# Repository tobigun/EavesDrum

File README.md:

<p align="center">
  No matter if you are E(a)ve or Ste(a)ve - drumming for e(a)veryone
</p>

<p align="center">

</p>

<!-- vscode-markdown-toc -->
- [Welcome to EavesDrum!](#welcome-to-eavesdrum)
  - [Downloads](#downloads)
  - [EavesDrum Trigger Module](#eavesdrum-trigger-module)
- [Features](#features)
- [Before You Start: Is EavesDrum What You Need?](#before-you-start-is-eavesdrum-what-you-need)
- [Getting Started](#getting-started)
- [Build Your Own EavesDrum Trigger Module](#build-your-own-eavesdrum-trigger-module)
  - [Use the Reference Design](#use-the-reference-design)
    - [PCB Ordering and Assembly](#pcb-ordering-and-assembly)
    - [Connector Harness](#connector-harness)
      - [Connector Module](#connector-module)
      - [Build your own adapter](#build-your-own-adapter)
      - [Wiring the Single Pad Connectors](#wiring-the-single-pad-connectors)
  - [Make Your Own Design](#make-your-own-design)
    - [How the Circuit Works](#how-the-circuit-works)
      - [Over-Voltage Protection](#over-voltage-protection)
      - [Voltage Divider / DC Voltage Offset Generator](#voltage-divider--dc-voltage-offset-generator)
      - [Example](#example)
- [Configuration](#configuration)
  - [Calibration](#calibration)
  - [Settings](#settings)
    - [Generic Settings](#generic-settings)
    - [Pedal Settings](#pedal-settings)
    - [Apply Presets](#apply-presets)
  - [Mappings](#mappings)
  - [Apply a Whole Configuration](#apply-a-whole-configuration)
- [Understand and Reduce Latency](#understand-and-reduce-latency)
  - [Reduce Hit Detection Latency](#reduce-hit-detection-latency)
  - [Reduce Audio Interface Latency](#reduce-audio-interface-latency)
  - [TL;DR](#tldr)
- [Firmware Development](#firmware-development)
  - [How to Build the UI](#how-to-build-the-ui)
  - [How to Build the Backend and Firmware](#how-to-build-the-backend-and-firmware)
  - [How to Simulate a Drum-Kit on a PC](#how-to-simulate-a-drum-kit-on-a-pc)
- [FAQ](#faq)
    - [Windows 10 NCM device driver](#windows-10-ncm-device-driver)
- [About This Project](#about-this-project)
- [Other Related Projects](#other-related-projects)
- [Libraries](#libraries)
- [Author](#author)
- [License](#license)

<!-- vscode-markdown-toc-config
	numbering=false
	autoSave=true
	/vscode-markdown-toc-config -->
<!-- /vscode-markdown-toc -->

## Welcome to EavesDrum!

EavesDrum is an open-source e-drum trigger module project designed for drummers and makers.

It allows you to connect a multitude of drum pads or piezo triggers and convert their signals into MIDI events.

The configuration of the module is simple and user-friendly, thanks to a built-in WebUI. You can adjust sensitivity, threshold, and other parameters directly from your browser—no need for complicated software or direct hardware programming.

The trigger module acts as a USB MIDI device - simply connect it to your notebook and use drum software of your choice (EZdrummer, Addictive Drums, SSD5, ...) to convert your notebook into a complete drum module.

### Downloads
- Trigger Module:
  - [PCB files](https://github.com/tobigun/EavesDrum/releases/tag/PCB-module-v1.1.1)
  - [Firmware](https://github.com/tobigun/EavesDrum/releases/latest)
- [DIY Optical Hi-Hat Sensor](doc/hihat.md)

### EavesDrum Trigger Module

DIY ultra-low-volume metal mesh cymbal setup:

Conventional rubber cymbal setup:

Low-volume cymbal setup:

System overview:

## Features

- **Drum Trigger Inputs:**
  - With the EavesDrum PCB, you can connect your drum pads or piezo sensors to 32 analog inputs.
  - Each input can be mapped individually, for example to 16 TRS (3-pin Tip-Ring-Sleeve) connectors or 32 TS (2-pin Tip-Sleeve) connectors.
  - The [default configuration](#connector-harness) uses the following drum setup:
    - Snare (1x TRS for head/rim + 1x TS for side-rim)
    - 5x Toms (each with 1 TRS for head/rim)
    - Kick drum (1x TS)
    - Ride (1x TRS for bow/edge + 1x TS for cup)
    - 4x Cymbals (each with 1x TRS for bow/edge + 1x TS for cup)
    - Hi-Hat (1x TRS for bow/edge + 1x TS for cup)
    - Hi-Hat Pedal resistive or optical (connected to a dedicated connector with 3.3V or 5V supply voltage)
- **Compatibility:**
  -  EavesDrum is compatible with a wide range of [Roland (only non-USB), Yamaha, ATV and EFNOTE pads](#pad-connectors).
  -  The following pads were tested:
     - ATV XD-P10M/P13M 2-zone Drums
     - ATV aD-C14/C16/C18 3-zone Cymbals
     - EFNOTE EFD-S12P 3-zone Snare (head, rim, side-rim)
     - Roland PDX-8 2-zone Drum
     - Roland KD-10 Kick Pad
     - Zeitgeist ZG ECP 13" 3-zone Cymbal
     - Zeitgeist ZG CAD Cymbals (although the edge triggers unreliably due to the switch design)
     - Zeitgeist ZG ZKD7 Kick Pad
     - Drum-tec Hi-Hat controller (resistive)
     - DIY optical sensor (TCRT5000 based)
       - See sections below for schematics and Gerber files.
     - DIY drums and cymbals
       - See sections below for schematics and Gerber files.
- **MIDI Output:**
  - USB Device (Default)
    - Connect EavesDrum to a PC and use a Drum Software like EZdrummer or Superior Drummer to convert the trigger signals to high quality drum sounds. 
  - USB Host
    - Connect a USB device to EavesDrum, e.g. a Drum Module and trigger sounds on that device
      - Tested with a Yamaha EAD-10
      - Device must be compatible with USB Full-Speed device. This does not apply to EFNOTE's 3/5/7 devices as they require a USB High-Speed device.
  - DIN 5-Pin
    - Connect legacy drum modules or devices that still have a DIN 5-pin connector and trigger sounds on them.
  - Bluetooth LE Client (Pico2W only)
    - This can be used to connect to a device that can act as a Bluetooth LE MIDI Server, e.g. EFNOTE's 3/5/7 drum modules.
  - Bluetooth LE Server (Pico2W only)
    - Activate the BLE Server mode and connect a smartphone or tablet to EavesDrum and trigger sounds in an app. This can also be used to connect a computer wireless.
      - Android (smartphone): works, but most MIDI apps will require the "MIDI+BTLE" app to use BLE as they do not support it directly.
      - Windows (PC): does not support BLE MIDI out-of-the-box. You will need a BLE connector app like [BLE-MIDI Bridge](https://github.com/Maxime-J/BLE-MIDI-Bridge) or [MIDIberry](https://apps.microsoft.com/detail/9n39720h2m05) together with a virtual loopback MIDI cable software like [loopMIDI](https://www.tobias-erichsen.de/software/loopmidi.html).
      - iOS (iPad): works with Garage Band out of the box
  - Guitar Hero Drum-Kit (SPI)
    - If you have an old Guitar Hero Drum-Kit (e.g. for the Wii), attach EavesDrum to the controllers internal SPI connector and play Guitar Hero on your retro console with your modern drum kit.
- **MIDI Mappings:** 
  - Mappings are freely customizable via the UI.
  - It already contains Midi-Mappings for:
    - Addictive Drums 2
    - BFD Player 1.2
    - EZdrummer 3 (which can probably also be used as a base for your own Superior Drummer 3 mapping)
    - Superior Drummer 3
    - MT Power 2
    - Steven Slate Drums 5 (SSD5)
- **Low Latency:**
  - Latency is mainly determined by your audio interface and the selected scan time. With a decent audio interface, you can [reach a total latency of about 8ms](#latency).
  - You can measure the latency of your setup with the latency measurement feature built into the UI.
- **Affordable:** you might be able to make an assembled trigger module for approx. 20€.
  - See the section [Build your own EavesDrum trigger module](#use-the-reference-design).
- **Supported Microcontrollers:**
  - Raspberry Pi Pico2
  - Raspberry Pi Pico2W (comes with a WIFI and Bluetooth module)
    - Required for MIDI over Bluetooth LE.
    - Also provides a WIFI Access Point to reach the EavesDrum WebUI wirelessly. 

- **Open Source:** Source code and PCB Gerber files are available for customization and extension.
- **WebUI Configuration:** Browser-based interface for setting up and tweaking trigger parameters such as sensitivity, threshold, retrigger prevention, and more. No app required as the UI runs directly on the trigger module.
  - Monitor the signal of your drum pads in real time so that you can see the effect of your settings.

  - Provides extensive settings options within a (hopefully) user-friendly layout.

  - Mappings can be adjusted individually or for the whole kit.

## Before You Start: Is EavesDrum What You Need?
**EavesDrum is for you if you:**
  - need more / additional trigger inputs to those that standard drum kits support.
  - want to mix drums from different vendors as most drum kits only work well with their own pads.
  - want to start drumming and do not want to pay a fortune for a drum kit.
  - want to diagnose or improve the trigger behavior of your drum pad.
  - have fun making stuff and just want to build your own drum kit or implement your own drum module features.

**EavesDrum might not be for you if you:**
  - want to use the module for live performances as it does not give any guarantee error-free operation at all times or conditions.
  - want a drum module that works standalone without a Notebook.
  - want a drum module that works out-of-the-box, as you will have to tweak the settings according to your pads via the UI.
  - need cross-talk cancelation, positional sensing or decay curves, as these features are not implemented (yet).

> [!IMPORTANT]
> **Disclaimer:** Although EavesDrum has been tested with various drum pads and setups, it remains a DIY hardware project and may behave differently depending on your specific configuration. Connecting this module to your equipment is done at your own risk. I cannot be held liable for any damage, malfunction, or injury resulting from its use. Please ensure compatibility and take appropriate precautions before integrating it into your setup.

## Getting Started

0. **Prerequisites:**
All you need is:
    - A computer with a drum software (see [MIDI Mappings](#midi-mappings) to give you a short overview).
      - A PC or Mac is recommended.
        - Although there is no minimum requirement, a slow CPU might increase the [Latency](#latency).
        - USB and Bluetooth LE is supported
      - An Apple iPad with Garage Band also works - either with USB-C (or an Apple Camera Connection Kit for Lightning connectors) or with Bluetooth LE.
      -  Android smartphones / tablets also work (via USB or Bluetooth LE) but lack good drumming apps.
    - A decent audio interface with low latency, preferably one with dedicated ASIO drivers. See [the section about latency](#latency) for more information.
    - Something to drum on, i.e. drum pads, cymbals and a Hi-Hat pedal. Or just a cheap piezo if you want to DIY your own drum.

1. **Build the EavesDrum trigger module:**<br/>
   - Either built it yourself or order it via a PCB manufacturer of your choice.
   - See section [Build your own EavesDrum trigger module](#use-the-reference-design) for schematics and Gerber files.

2. **Download & Flash the firmware:**<br/>
   - [Download the firmware for your Pico board from the Release download section](https://github.com/tobigun/EavesDrum/releases/latest).
   - Press the BOOTSEL while connecting your Pico Board via USB to enter the bootloader mode.
   - The board will now be detected as an USB flash drive.
   - Drag & Drop the firmware .uf2 file onto the drive.
3. **Start the WebUI:**<br/>
   - Connect EavesDrum to a computer, tablet or smartphone
     - via USB: EavesDrum will be detected as a network device
     - via WIFI AccessPoint (only with Pico2W)
       - The AccessPoint (AP) can be activated by pressing and holding the WIFI button at power-up until the network LED lights up. For security and performance reasons, the AP is only active for one session until the module is powered down.
       - Connect to the AP named "EavesDrum". No credentials are required.
   - Open your browser and navigate to the WebUI by entering either
     - the static IP: http://192.168.7.1 (USB) or http://192.168.4.1 (WIFI AP)
     - the DNS name http://eaves.drum</a>.
     - **IMPORTANT**: if you are using Windows 10 you have to install the USB network drivers manually to reach the WebUI. See the [FAQ](#faq) section below for more info. 
4. **Calibrate:**<br/>
   - [Calibrate the voltage offset with the UI Wizard](#calibration)
5. **Connect Drums:**<br/>
   - Connect your drum pads or triggers to the EavesDrum hardware.
6. **Configuration:**<br/>
   - Adjust [settings](#settings) and [MIDI mappings](#mappings).
7. **Play:**<br/>
   - Once configured, start playing and enjoy!

## Build Your Own EavesDrum Trigger Module
### Use the Reference Design
**Schematics of the trigger module with 32 inputs:**

You can find the schematics and pcb files in the `schematics/module` directory. They can be viewed and edited with [KiCad](https://www.kicad.org/).

**Bill of material (BOM):**

| Component | Designator | Quantity | Price / Unit | Price Total | Comment |
| --------- | ---------- | -------- | ------------ | ----------- | ------- | 
| Raspberry Pi Pico 2(W)(H) | A1 | 1 | 5€ / W: 7.50€ | 5€ / W: 7.50€ | Use a Pico2W if you want WiFi and Bluetooth LE, otherwise a Pico2 is enough.<br>- There is also a "H" variant for ~1€ more with an already soldered header<br>- Pico1 is not recommended due its outdated performance. |
| 20-pin Header (male)<br>20-pin Header (female) | J4, J5 | 2 | 0.20€<br>0.30€ | 1.00€ | Optional but recommended. <br>- Socket your Pico so that it can be replaced if it is damaged or if you want to exchange it by another variant.<br>- The male header is not needed if one of the Pico "H" variants is used. |
| HC4067 | U1, U2 | 2 | 1.00€ | 2.00€ | Multiplexer. Each provides 16 inputs.<br>Available from many vendors with HC4067 in the name (e.g. CD74HC4067M). Make sure it is the SO-24 package. |
| BAT54S | D1.0 - D1.15<br>D2.0 - D2.15 | 32 | 0.05€ | 1.60€ |Prefer the ones with a forward voltage (VF) of 800mV@100mA over those with 1V@100mA but probably any vendor and type will work.|
| LED (red) | D3 | 1 | 0.08€ | 0.08€ | Use any color of your choice. THT or SMD 0805 / 0603 packages are supported. |
| LED (white/blue) | D4 | 1 | 0.10€ | 0.10€ | Use any color of your choice. THT or SMD 0805 / 0603 packages are supported. |
| LED (yellow) | D5 | 1 | 0.10€ | 0.10€ | Use any color of your choice. THT or SMD 0805 / 0603 packages are supported. |
| Push Switch | SW1, SW2, SW3 | 3 | 0.15€ | 0.45€ |6x6mm. Only the `RESET` button is used at the moment. |
| Potentiometer 5k | R3, R6 | 2 | 0.35€ | 0.70€ | Supports Piher PT10 (10mm) / PT6 (6mm) or Bourns TC33 (SMD) |
| Potentiometer 100k | R11 | 1 | 0.35€ | 0.35€ | Supports **only** Piher PT6 (6mm) or Bourns TC33 (SMD) |
| Resistor 10 Ohms | R17 | 1 | 0.03€ | 0.03€ | SMD 0805 package, 125mW, 1%.<br>For MIDI 5-pin DIN connector |
| Resistor 33 Ohms | R18 | 1 | 0.03€ | 0.03€ | SMD 0805 package, 125mW, 1%.<br>For MIDI 5-pin DIN connector |
| Resistor 330 Ohms | R5, R8, R13 | 3 | 0.03€ | 0.09€ | SMD 0805 package, 125mW, 1% |
| Resistor 1 kOhms | R1.0 - R1.15<br>R2.0 - R2.15 | 32 | 0.015€ | 0.48€ | SMD 0805 package, 125mW, 1% |
| Resistor 2.7 kOhms | R4 | 1 | 0.03€ | 0.03€ | SMD 0805 package, 125mW, 1% |
| Resistor 4.7 kOhms | R9, R14 | 2 | 0.03€ | 0.06€ | SMD 0805 package, 125mW, 1%.<br>Use different values to adjust brightness of LEDs D3 (R9) and D5 (R14) to your liking. |
| Resistor 10 kOhms | R10 | 1 | 0.03€ | 0.03€ | SMD 0805 package, 125mW, 1%<br>Use different value to adjust brightness of LED D4 to your liking. |
| Resistor 15 kOhms | R15, R16 | 1 | 0.03€ | 0.06€ | SMD 0805 package, 125mW, 1%.<br>For USB-Host connector |
| Capacitor 10 µF | C1, C2 | 2 | 0.04€ | 0.08€ | SMD 0805 package, >=25V, X5R (or X7R)
| D-Sub HD 44-pin Connector, right-angled, female | J0 | 1 | 2.50€ | 2.50€ | Alternatively, you can use any connector of your choice via the 2x25 pin IDC header (J2). |
| USB-A socket, right-angled | J1 | 1 | 0.15€ | 0.15€ | Socket for USB-Host. |
| Header 2x25 pins (male) | J2 | 1 | 0.33€ | 0.33€ | Expansion port (Optional).
| 3-Pin Header (female) | J3 | 1 | 0.15€ | 0.15€ | UART serial debug output.
| DIN 5-pin female 180° | J7 | 1 | 0.85€ | 0.85€ | Connector for MIDI Serial DIN Output. |
| PCB | - | 1 | ~5€ (Germany) | ~5€ | See the section [PCB Ordering and Assembly](#pcb-ordering-and-assembly) for more info|
| **Total** |||| ~22€ || 

If you are located in Germany, check prices at Reichelt (that's where the prices from above are from), Pollin, Conrad. Globally Mouser and Farnell might be your friend.

#### PCB Ordering and Assembly
All you need to order your Trigger Module PCB for assembly are the following files:
- GERBER File
- BOM File (Bill of Material)
- CPL File (Component Placement List)

These files are available on the [PCB Module 1.2 Release Page](https://github.com/tobigun/EavesDrum/releases/tag/PCB-module-v1.2).

**To order the PCB:**
- Open the website of a PCB manufacturer.
  - The most famous ones are probably JLCPCB and PCBWay from China.
  - There is also Aisler (Germany), EuroCircuits (Europe) and probably more if you want to produce your PCB in Europe instead of China.
  - Choose whatever suits you best.
- Upload the GERBER zip-file. The site should show you a preview of the PCB now.
- You can leave the default settings.
  - (Recommended) Change `Surface Finish` from `HASL (with lead)` to `LeadFree HASL` to protect our environment from toxic lead
- For delivery "EuroPacket" or "Global (Standard) Direct" might be your choice.
  - Both variants will ship your PCBs together with other PCBs in a big package to an importer in your home country (or a neighbored country). The package will then be split into smaller packages and sent to you. This is cheaper and will probably also save you the hassle of customs as this will be done by the importer.
  - The shipment time is a bit longer than with other more expensive delivery options. But with all options the parcel will probably spent several days in the customs office, so time savings is not that much noticable.

*Examples:*
- JLCPCB: 4€ - Coupons + Shipping/Taxes
  - Shipping to Germany: Global Standard Direct: 1.50€ / EuroPacket: 5.50€ + Tax: ~1€
- PCBWay: 5€ - Coupons + Shipping/Taxes
  - Shipping to Germany: ~5€ with Global Direct + Tax: ?

Due to the varying discount by coupons, prices of JLCPCB and PCBWay my vary. So check both.

**Assembly**
It is possible to assemble the PCB on your own by hand-soldering without special equipment. The only tricky part is the HC4067 SMD packages and the SMD resistors and capacitors. While the latter is quite easy, the HC4067 requires some experience.

You can also let JLCPCB or PCBWay assemble the PCB as you already order the PCB there.

*Example:*
- JLCPCB: 5 assembled PCBs including parts cost about 106€ (excl. shipping/tax), so approx. 21€ per PCB.
  - Note that the minimum amount of assembled PCBs per order is 2

If you want an assembled board it is best to organize a collective purchase order to split the cost. I created a [forum discussion where you can organize an order](https://github.com/tobigun/EavesDrum/discussions/1).

**To order an assembled PCB:**
- Perform the same steps as for the normal PCB but select "PCB Assembly".
- If you use JLCPCB in the next step you are asked for the BOM and CPL files that you have to upload.
- Some parts might currently not be available. There is most likely an identical component / chip from a different vendor that you can select in this case.
- In the next step check the component placements and submit your order.
- After a review an engineer might contact you if there are questions about the design (that was the case in my order).

> [!NOTE]
> Also take a look at the [DIY Optical Hi-Hat Sensor PCB](doc/hihat.md). You might want to get both PCBs with one order.

#### Connector Harness

In addition to the trigger module you will have to build an adapter to connect the drum pads.

##### Connector Module

The easiest way to achieve this is to build the connector module:

You can find more information about the connector and the files to order the (assembled) PCB on the  
[connector release page](https://github.com/tobigun/EavesDrum/releases/tag/PCB-connector-v1.0).

##### Build your own adapter

But you can also build your own adapter. Here is the pin out of the D-Sub HD 44 pin connector:

The pin names consist of the multiplexer input IDs (in1_x: input x of Multiplexer MP1, in2_x: input x of Multiplexer MP2).

You can either solder jacks directly to a D-Sub connector or you can build an adapter to one of the cable harnesses that come with drum modules.

This is the default configuration for the outputs:

| Jack | Pins | Assignment |
|-----------|------|------------|
|1| in1_0, in1_1, in1_2 | Snare (Main, Rim, Side-Rim) |
|2| in1_3, in1_4 | Tom 1 (Main, Rim) |
|3| in1_5, in1_6 | Tom 2 (Main, Rim) |
|4| in1_7, in1_8 | Tom 3 (Main, Rim) |
|5| in1_9 | Kick Drum |
|6| in1_10, in1_11, in1_12 | Ride (Bow, Edge, Cup) |
|7| in1_13, in1_14, in1_15 | Cymbal 1 (Bow, Edge, Cup) |
|8| in2_0, in2_1, in2_2 | Cymbal 2 (Bow, Edge, Cup) |
|9| in2_3, in2_4, in2_5 | Cymbal 3 (Bow, Edge, Cup) |
|10| in2_6, in2_7, in2_8 | Hi-Hat (Bow, Edge, Cup) |
|11| in2_9, in2_10 | Tom 4 (Main, Rim) |
|12| in2_11, in2_12 | Tom 5 (Main, Rim) |
|13| in2_13, in2_14, in2_15 | Cymbal 4 (Bow, Edge, Cup) |
|Pedal| adc2, +3.3V/5V (optical only) | Hi-Hat Pedal (resistive or optical)<br>- For resistive controllers: adjust the `ADC2 DC offset` potentiometer to the (+) direction (~4kOhm)<br>- For optical (TCRT5000) controllers: adjust the `ADC2 DC offset` potentiometer to the middle (~69kOhm)<br>This will adjust the sensitivity of the ADC2 channel. You can fine-tune this setting in the UI later. |

> [!INFO]
> The layout for the older D-Sub 37 pin connector of board revisions v1.1.x can be found [here](https://github.com/tobigun/EavesDrum/tree/PCB-module-v1.1.1#connector-harness)

##### Wiring the Single Pad Connectors

The wiring of **Snares and Toms** is straightforward in most cases
- Almost all companies use the Roland style 2-Piezo 1xTRS layout
- Yamaha uses switches for Edge and Side Rim
- EFNote adds a dedicated Side-Rim zone with another Piezo

<table>
<thead>
  <tr>
    <th>Tom/Snare</th>
    <th>Main/Head (Piezo)</th>
    <th>Edge</th>
    <th>Side-Rim</th>
    <th>EavesDrum Setting</th>
  </tr>
</thead>
<tbody>
  <tr><td>Generic 1-Zone</td><td>Tip</td><td>-</td><td>-</td><td>Drum / 1-Zone / Piezo</td></tr>
  <tr><td>Roland 2-Zone</td><td>Tip</td><td>Ring</td><td>- (Cross-Stick sound is generated by module)</td><td>Drum / 2-Zones / 2 Piezos</td></tr>
  <tr><td>Yamaha 3-Zone</td><td>Tip</td><td colspan='2'>Ring (Switches for zones are multiplexed by a 10k resistor)</td><td>Drum / 3-Zones / Piezo + 2 Switches (1x TRS)</td></tr>
  <tr><td>EFNOTE 3-Zone</td><td>Tip (Main Jack)</td><td>Ring (Main Jack)</td><td>Tip (Side-Rim Jack)</td><td>Drum / 3-Zones / 3 Piezos</td></tr>
</tbody>
</table>

**Cymbals** (with 3-Zones) follow two main connection styles:
- Roland style with 2x TRS Jacks (labeled "Bow/Edge" and "Bow/Bell")
- Yamaha style with 1x TRS Jack. Bell and Cup switch connected to the "Ring" pin (multiplexed by a 10k resistor)

If you have only a one or two zone cymbal the pin layout is the same for both vendors.

<table>
<thead>
  <tr>
    <th>Cymbal</th>
    <th>Bow (Piezo)</th>
    <th>Edge Switch</th>
    <th>Bell/Cup Switch</th>
    <th>EavesDrum Setting</th>
  </tr>
</thead>
<tbody>
  <tr><td>Generic 1-Zone</td><td>Tip</td><td>-</td><td>-</td><td>Cymbal / 1-Zone / Piezo / No Choke</td></tr>
  <tr><td>Generic 2-Zone</td><td>Tip</td><td>Ring</td><td>-</td><td>Cymbal / 2-Zones / Piezo + Switch / Choke: Edge</td></tr>
  <tr><td>Roland 3-Zone</td><td>Tip (Jack "Bow/Edge")</td><td>Ring (Jack "Bow/Edge")</td><td>Ring (Jack "Bow/Bell")</td><td>Cymbal / 3-Zones / Piezo + 2 Switches (<b>2x</b> TRS) / Choke: Edge</td></tr>
  <tr><td>Yamaha 3-Zone</td><td>Tip</td><td colspan='2'>Ring (multiplexed by a 10k resistor)</td><td>Cymbal / 3-Zones / Piezo + 2 Switches (<b>1x</b> TRS) / Choke: Edge</td></tr>
</tbody>
</table>

See also:
- [Cymbal wiring diagram at edrums.github.io](https://edrums.github.io/en/diy/cymbal_switch/) for the wiring difference between Roland and Yamaha cymbals.
- [Yamaha compatibility matrix](https://de.yamaha.com/de/download/files/2094396/) for an overview of the Tom and Cymbal models

### Make Your Own Design

In case you do not want to use the reference design or you just need a few inputs, you can also design your own trigger module and just use the firmware.
The base circuit for each input consists of the following parts:

Please note that "~2,7k" for R1 in the schematics means that the variable resistor should be adjusted to this value. The nominal value of the resistor should be about 5k to have some range for the adjustment.

You might also be able to build this on a breadboard for first experimentation.

#### How the Circuit Works
Skip this section if you are not interested in the electronic background of the circuit.

##### Over-Voltage Protection
- Two clamping diodes restrict the signal to the range between 0V - 3.3V
  - Protects the ADC input pins of the microcontroller
  - Prevents cross-talk between inputs if a Multiplexer (e.g. 74HC4067) is used
- Note that Schottky diodes with a low forward voltage have to be used here
  - They react faster than a conventional (Silicon P-N-junction) diode to over voltage spikes
  - The BAT85, BAS85 (SMD variant of the BAT85) and BAT54S (two diodes in one SMD package) diodes work fine

##### Voltage Divider / DC Voltage Offset Generator
- The resistors R1 and R2 form a voltage divider that halfs the operation voltage (Vcc=3.3V) to generate a ~1.65V DC offset voltage
  - This is necessary to sample the full signal with its positive and negative half-wave
  - Note that R1 is a variable resistor (potentiometer) as the circuit is usually not that perfect that R1=R2 gives you half the operation voltage as it should in theory
- Together with R3, R1 and R2 scale the voltage of the piezo to the range of 0V - 3.3V that can be sampled by the ADC
  - This is necessary as the voltages of a piezo can be rather high.
  - If you want to play with the values there is an [LTSpice simulation here](doc/simulation/drum-trigger.asc) but keep in mind that the piezo model does not act like a real one.
- Simpler approaches without an offset voltage are also possible, e.g. by just clamping the signal with a zener diode to just keep the positive half-wave of the signal
    - Although this works, you will have to pay attention to the polarity of the piezos
    - If the piezo starts with a negative half-wave, you will miss it and thus will add latency of approx. 1ms
    - This is even worse, if you use two piezos for head and rim, as the wrong zone might be triggered if the first half-wave of one piezo is missing but missing for the other.

##### Example
Here is a simple example with a high intensity hit on a snare drum: The left shows the input signal that is offset by 1.65V and it fits nicely into the 0V - 3.3V range. On the right you see the display in the UI. All the details of the signal are maintained. Note that the firmware maps the negative part of the signal to the positive y-axis so that the thresholds can be edited more easily.

## Configuration

### Calibration
Before you can start you have to first adjust the DC voltage offset so that the signal level is at 0% when no pad is hit. But no panic - the process is easy and only has to be done once.

For this open the WebUI, open the settings page (should be open by default) and click on `Calibrate` in the `Monitor` panel and follow the instructions.

At the beginning the signal graph will probably look like this, with a signal level above 0% (here 10%):

Now turn the potentiometer labeled `ADC0 DC offset` (R3) with a screwdriver. Only if turned in the correct direction, the signal level will decrease, otherwise it will increase. So turn the potentiometer until the signal level reaches 0%. If you turned too much, the signal level will increase again - in this case turn in the opposite direction.

The signal graph should now look like this - with a signal level of 0%:

Now the calibration is completed.

> [!NOTE]
> Do not worry if the signal is not totally clean and has a bit of a ripple in the 1% or 2% range. This can be compensated with the thresholds later.
> If you do not reach the 0% level at all, your trigger module might be faulty.

### Settings

To optimize the trigger behavior for your pad, go to the settings page and open the panel of the pad you want to adjust.

First assure that the Drum type (here: Drum / 3-Zones / 3 Piezos) is correct. If you are not sure, check [the section about the different pad connectors](#pad-connectors) to see what the type should be.

Mark the pad as monitored (the record button on the right top of the pad's panel). This way you can see the signal graph (left) and hit graph (right) in the `Monitor` panel whenever you hit the monitored pad. Right next to the hit graph is the hit history which shows you the last hits. You can also click on one of the last hits to see the graphs again.

If you click on `Show All Pads` on the top, you can see hits on every pad, no matter if it is monitored or not.

#### Generic Settings

- **Main/Head/Rim/Edge/Cup/... Range**: trigger range for each zone
  - The **min. value of the range** specifies the sensitivity.
    - You should set it as low as possible without having the pad trigger when you do not hit it.
  - The **max. value of the range** specifies the signal level that marks 100%.
    - Set it in a way that you can reach a signal level of 100% when you hit the pad the hardest way you would in your playing style.
    - If you set the max. too low, the detected signal level will be 100% even if you did not hit the pad with the highest intensity.
  - If you enable monitoring for the pad it should be easy to find the correct values.
  - For cymbals with switches for edge and cup you will only have a **minimum threshold** for each switch instead of a range.
    - This determines at which level the switch is considered to be closed or opened.

- **Scan Time**: Determines the time to search for a peak (Scan phase).
- **Mask Time**: Blocks hit detection for the given time (Mask phase).
  - Can be used to reduce false retriggers.
  - The Mask phase starts after the Scan phase.
  - The Mask is applied to all zones of the pad.
- **Decay Time**: Blocks hits with a hit velocity below the given decay curve (Decay phase).
  - In contrast to the Mask phase that blocks all hits, this only blocks hits selectively.
  - It can be used to define a longer decay phase where reverberations of the last hit can be blocked but new hits are still possible if they are strong enough.
  - The Decay phase starts after the Mask phase.
  - The Decay curve is applied to all zones of the pad.
- **Decay Curve**: The curve that defines how the detection threshold decreases during the decay phase.
  - **Linear**: The further the decay phase progresses, the lower the required hit strength becomes for a hit to be detected. 
    - The phase begins with a detection threshold equal to the highest signal value detected during the scan phase (the peak).
    - It ends with a detection threshold equal to the minimum detection threshold.
    - Throughout the decay phase, the threshold is linearly reduced from the peak value down to the minimum threshold.
- **Curve Type**: Lets you change the trigger behavior for low or high intensity hits, i.e. you can shift the sensitivity more to the lower or higher intensities.
- **Head/Rim Bias**: Sets whether to prefer head or rim sound when the signals of both to not indicate a clear winner.
  - This is useful to assure that rimshots trigger the rim sound.
  - Move the bias more to the rim (i.e. to the right), the rim zone will more likely be triggered if both zones were hit at once.
  - Only available for drums (i.e. snares and toms) with at least two zones.

> [!IMPORTANT]
> When you change settings they will be applied immediately but they will be reset to the old values when EavesDrum reboots or loses power. To keep the settings you have to save them with the "Save" Button (SD-Card icon) in the top Icon Bar.

#### Pedal Settings
The settings for the Hi-Hat pedal are different from the settings of the pads.

- **Pedal Range**: determines the offset and threshold for the lowest and highest signal level
  - Do not touch the Hi-Hat pedal for the open position.
  - Adjust the **min value** of the `Pedal Range` so that the corresponding marker in the monitor's signal graph is slightly above the current pedal signal and the Pedal value in the hit graph is at 0%.
  - Next, close the Hi-Hat pedal.
  - Now adjust the **max value** of the `Pedal Range` so that the corresponding marker in the monitor's signal graph is slightly below the current signal and the hit graph shows 100%.
  - When you move the pedal now, you should get the full range between 0% and 100% in the hit graph, and it should stay at 0% when open and at 100% when closed.
- **Move Detection Tolerance** this determines how much the pedal has to be moved to change its value. A smaller tolerance gives you a higher resolution but is more prone to noise in the signal.
  - Press the Hi-Hat pedal to a position between open and closed. Try to keep this position - the value in the hit graph should not change. If it does, you might decrease the tolerance until the hit graph value is stable.
- **Pedal State Thresholds** and **Chick Detect Timeout**:
  - When the pedal travels from the `Almost Closed` position to the `Closed Position` a "Chick" sound detection takes place.
  - The faster the pedal moves from `Almost Closed` to `Closed` the higher the intensity of the "Chick" sound will be.
  - If the time between both states is higher than **Chick Detect Timeout**, then no sound will be played.
  - If you do not want a "Chick" sound, you can disable it on the Mappings Page by setting the sound for the "Chick" to `None`.

To see the effect of the settings, monitor the pedal with the record button:

#### Apply Presets
In the folder `config/presets` you can find some presets for some pads. You can apply them by dragging them from Windows Explorer to the settings panel of a pad.

### Mappings

With the Mappings page you can change the MIDI mappings of each pad.

Select the MIDI note of the zone to the desired value. You can trigger the note via the UI by pressing the "Play" button to preview the sound.

> [!IMPORTANT]
> When you change mappings they will be applied immediately but they will be reset to the old values when EavesDrum reboots or loses power. To keep the settings you have to save them with the "Save" Button (SD-Card icon) in the top Icon Bar.

**Apply Drum-Kit Mappings**
You can change the mappings of all pads in the drum-kit at ones if you drag & drop a mapping file (see folder `/config/mappings`) to top border (aka the Icon Bar) of the UI. This way you can switch between the mappings of the drum softwares easily.

Alternatively you can also click on the "Apply Config File" button in the top Icon Bar to open the same file drop area that appears if you drag & drop a file.

If you drag & drop the mappings file onto a pad instead of the top bar, only this pad's mappings will be changed:

**Roles**
Note that the mappings are assigned to a `role` (e.g. Snare, Tom1, ...) and not to a pad directly. As the drum kits differ in number and type of pads it would be rather difficult to have generic mapping files if there is no common denominator for every drum. This is what the role is for: it specifies the role of the drum in the drum kit, so that you have the correct mappings assigned to the drum when you switch from one mapping file to another.

### Apply a Whole Configuration
If you want to have more control over a configuration you can download the active configuration with the "Download" icon in the top Icon Bar. Then do you modifications on the downloaded YAML file and upload it again by either clicking on the "Apply Config File" button in the Icon Bar or by Drag & Drop of the config to the Icon Bar.

This way you can Backup & Restore your config whenever you do a firmware update.

## Understand and Reduce Latency
At a speed of sound of about 343 m/s, the sound travels 34 cm in 1 ms, so a little less then the length of a drum stick. It seems that everything up to [5 ms is not noticeable and most drummers still have no problem with 10 ms](https://forums.steinberg.net/t/ab-welcher-latenz-bemerkt-ihr-eine-verzogerung-und-ab-wann-stort-die-euch/105517/45). So you want the latency to be as low as possible or at least below 10 ms.

If you look at the signal path there a quite some components involved from the hit to the drum until you hear the sound from the speaker. This is round trip time (RTT) of your system which defines the latency of your signal.

1. The **hit detection** by the trigger module will take a fixed time - the scan time that you selected in the pad's settings and that is by default 3 ms.
1. The time it takes the trigger module to **generate and transfer a MIDI message to the computer via USB** is negligible as it is only a small fraction of a ms.
2. Although the **sound processing** might also take some time I did not notice a vast differences between the drum softwares.
3. The audio latency from your drum software to the **audio interface** is the biggest contributor to latency.

### Reduce Hit Detection Latency
The time the trigger module waits for a peak to detect a hit can be configured for each pad. The default of 3 ms was chosen so that it works with most drum pads.

If you take a look at the screenshot of the Monitor below you might notice that the piezo signal for some pads reaches its peaks only after 1, 2 or even 3 ms. 

So if you set the scan time too low, you might get wrong results. Decrease the scan time in small amounts and check if the hit strength are still detected correctly.

### Reduce Audio Interface Latency
The Audio Interface latency depends on the **number of buffers** the software, drivers and audio interface uses and the **buffer size**.
  - Dedicated audio interfaces for musicians are optimized for low latency and offer better (ASIO) drivers.
  - The bigger the buffer the less error-prone is the playback, even if the CPU is currently doing some other stuff. But every buffer and every byte in the buffer will increase the latency.

The best way to reduce latency is to **reduce the buffer sizes**. The goal is a **latency of 5-6 ms** for this part of the signal chain.
  - On **Windows** this is **only possible** without crackling and dropouts **with ASIO drivers**. So make sure your audio device has dedicated ASIO drivers.
  - Do not waste your time with **WASAPI** or **DirectSound** drivers. WASAPI (Low-Latency) resulted in 69ms, WASAPI (Exclusive Mode) in 34.9ms. DirectSound was even worse. Same device with ASIO was about 6ms.
  - You can try **[ASIO4All](https://asio4all.org/)** if you want to start with an existing interface that does not come with ASIO drivers - but keep your expectations low. With the Realtek soundcard built into one of my notebooks I could not get the latency below 35 ms with ASIO4All which is unusable.

**Select ASIO as the output type** in your drum software and start with the lowest audio buffer size.
  - Trigger the pads really quick and try every pads if you hear some crackling or dropouts on any of them.
  - Also check if the audio quality is still ok or if it sounds muffled, ...
  - If you notice audio problems (**crackling, muffling, popping, dropouts**)
    - Make sure that no other CPU-intensive software is currently in use.
    - Also make sure that your CPU is suited for the task (i.e. you CPU load is not too high)
    - Although my old Intel Core i7-7500U (2.7 GHz) Ultrabook CPU from 2016 works fine as drum computer most of the time, it seems to stutter sometimes if I select the lowest buffer size. Something I have not noticed with my newer Intel Core i7-1260P (2.1 GHz, 12 Cores) from 2022.
    - If you have a modern i7 (and probably i5) CPU you should be fine. Same with an Apple M1 CPU.
  - If you still notice audio problems **increase the sample size step by step** until you get a stable output.

Note that the latencies that your ASIO driver displays for each buffer size (e.g. 64 samples -> 1.5 ms) is only the **theoretical minimum** with this setting. In reality the value is much higher (e.g. for my device 5 ms instead of the 1.5 ms). You can measure the system latency if you want to be sure (see below)

Sometimes you can further reduce the latency by **increasing the sample rate** (so 192kHz, 96kHz or at least 48kHz instead of 44.1kHz), but this might not always give you the expected result.

Last but not least the **OS** might also be a factor. If you have the choice try Mac OS X or iOS - it might perform better due to its superior audio architecture.

### TL;DR

To reduce the latency, use a decent Audio interface, use dedicated ASIO drivers, reduce the sample size and try to increase the sample rate. You should get the output latency of the audio device to about 5-6 ms with ASIO on Windows. So with a scan time of 3 ms this will be 8-9 ms. If you are still not satisfied with this, try to reduce the scan time of the pads.

You can test the latency of your system with the latency measurement feature, built into the UI. Open the `Settings` page and click on `Check Latency` on top of the `Monitor` panel. The wizard will guide you through the procedure.

---

Below are the measurement results from the audio interfaces that I own. Maybe it will give you an idea what to expect:

|Device            |Sample Rate|Buffer Size|ASIO driver|Latency|Comment|
|------------------|-----------|-----------|-----------|-------|-------|
|Behringer UMC204HD|**48kHz**|32 (0.7ms)|UMC ASIO|5.7ms||
|Behringer UMC204HD|**96kHz**|32 (0.3ms)|UMC ASIO|5.2ms||
|Focusrite Scarlett Solo 4th Gen|48kHz/96kHz/192kHz|16 (3.8-4.9ms)|Focusrite USB ASIO|5.0ms|No big difference between sample rates. One notebook preformed best with 192kHz, the other with 48kHz (dropouts with higher rate). Thunderbolt ASIO did not work|
|NUX Mighty Plug (Pro)|48kHz|8 (0.2ms)|NUX Audio|6.9ms|A guitar effect plug, so maybe not what you want.|
|Terratec Aureon 5.1 USB MK.2|48kHz|64 (1.3ms)|ASIO4All|5.9ms||
|Conrad UA0078 (CMedia CM108 chip)|48kHz|64 (1.3ms)|ASIO4All|6.6ms||
|Realtek HD Audio (HW Dev-ID 0x0293)|44.1kHz|64 (1.5ms)|ASIO4All|6.4ms|Could be an ALC293. The latency was not constant between tests and reached in a few instances 12, 23 and even 40ms. Realteks ASIO driver was not available on the computer.|
|EFNote 3 as Audio Interface|48kHz|32 (0.7ms)|EFNOTE|8.2ms|Measured on my old Notebook with an Intel Core i7-7500U (2.7 GHz) CPU from 2016. Got about 13ms on my newer Notebook with the same setup.|
|Yamaha EAD10|44.1kHz|48 (1.1ms)|Yamaha Steinberg|16.1ms|Tested on two different systems with same result.|
|Noname USB-C headphone adapter (AB13X)|44.1kHz|64 (1.5ms)|ASIO4All|23.8ms||
|Realtek HD Audio (HW Dev-ID 0x0294)|44.1kHz|64 (1.5ms)|ASIO4All|34.9ms|Could be an ALC294. Realtek's ASIO driver crashed, so I had to use ASIO4All.|

*Notes*:
* Measured on my Notebook with an Intel Core i7-1260P (2.1 GHz, 12 Cores) from 2022 (if not otherwise stated)
* The measurements were performed multiple times and the results varied slightly (~0.5 - 1ms) between tests. I took a result with a representative value.
* The folder `doc/latency` contains screenshots of all tests.

There is a [forum where you can post your own latency measurements](https://github.com/tobigun/EavesDrum/discussions/2).

Also check out the [Latency Test by Secret Sauce on Youtube](https://www.youtube.com/watch?v=DEgUQVjkk2g) ([Full results](https://www.dropbox.com/scl/fi/n60srm83qz4fhdilr7zsh/Round-Trip-Latency-Tests-Round-Trip-Latency-Tests.pdf?rlkey=s357wgnl4lxkiuw7nl1j95wcx&e=1&st=j8oy9cmj&dl=0)). Here some notable results:

|Device|Sample Rate|Buffer Size|Latency|
|------|-----------|-----------|-------|
|Arturia MiniFuse 2|48kHz / 96kHz / 192kHz|32|5.0ms(@48kHz) / 3.4ms(@96kHz) / 2.8ms(@192kHz)|

**Conclusion**
> - Dedicated devices (Focusrite Scarlett Solo / Behringer UMC204HD) performed best.
> - Drum Modules (at least EFNote 3 and Yamaha EAD10) might not be suited to be used as low latency audio output interfaces.
> - The results can vary between Computers and sometimes a 9 year old Computer can give you better results than a new one (see EFNOTE 3).
> - Although some ASIO4All performed quite well and I did not notice any crackling during the short test, I would not recommend them, as crackling is still likely with them. But it might be a start if you already own them.

## Firmware Development
EavesDrum already comes with pre-built releases. So you do not need to build it yourself. In case you want to change the code, here are the steps to build the firmware yourself.

### How to Build the UI
- Install [NodeJS](https://nodejs.org/en)
- Open the project directory in a terminal (cmd or git bash)
- Change directory to the `webui` directory
  - `cd webui`
- Install the dependencies with NPM
  - `npm install`
  - (This will require NodeJS and NPM, which should be installed with NodeJS. If the command does not work, make sure that the binary path of NodeJs is in your environment PATH)
- Now build the UI with `npm run build`. The result should be written to the `data` directory in the root directory of the project
- You can also start `npm run serve` to start a server on `http://localhost:8080`. This will proxy requests either to the [PC simulation](#simulation) or to the hardware device, depending on the selected target in `vite.config.ts`.
  - If you set the target to the hardware device you can test UI changes without building a new firmware.

### How to Build the Backend and Firmware
- Download and install [Visual Studio Code](https://code.visualstudio.com/)
- Open Visual Studio Code and install the [PlatformIO](https://marketplace.visualstudio.com/items?itemName=platformio.platformio-ide) extension
- Download the EavesDrum code from this repository via Git or zip
- Open the root directory of this project (the one with the `platform.ini` file) in Visual Studio Code
- Select the target ("pico2" is recommended)
- Press `build`
- Press `upload`
  - Per default the Raspberry Pi Debug Probe is selected to upload the firmware
  - Change `upload_protocol` from `cmsis-dap` to `mbed` in the `platform.ini` file (section `pico-base`) if you do not have a Debug Probe and want to upload the firmware per USB instead. This will create an UF2 file and flash it via the flash-drive in bootloader mode.
    - If the upload fails, try to enter the bootloder manually by pressing the `BOOTSEL` button of the Pico when connecting it via USB (or alternatively pressing the `RESET` button if you use the EavesDrum PCB).
- Click on the `Platform` / `Upload Filesystem image` task in the PlatformIO tab (click the side-bar icon with the PlatformIO ant logo to open the menu first)
  - Important: this requires that the WebUI is setup first. Follow the steps of [How to build the UI](#how-to-build-ui) until `npm install`. A manual build is not required, as the `Upload Filesystem image` task will trigger a build for you.

### How to Simulate a Drum-Kit on a PC
There is also a simulation of a drum kit for PC in case you do not want to test on real hardware.

**Build the simulation:**
- Install the GCC/G++ Toolchain for Windows via MSYS2
  - https://code.visualstudio.com/docs/cpp/config-mingw#_installing-the-mingww64-toolchain
- Install portmidi in the MSYS2 shell:
  - `pacman -S mingw-w64-x86_64-portmidi`
- Follow the steps of [How to build the firmware](#how-to-build-fw) until the build step but select the `native-win` environment instead

**Run the simulation:**
- The `upload` button will start the application
- The WebUI will be reachable on port 80 via http://localhost
- Some actions can be triggered via the terminal:
  - A pad hit can be triggered with the number keys (1: first pad, 2: second pad, ..., 0: 10th pad). The zones are triggered randomly
  - Press `Shift` + \<number> to choke the corresponding pad
  - Press `+` or `-` to increase or increase the offset of the monitored pad. This is useful to simulate pedals
  - Press `#` to select the amount of Jitter in the signal of the monitored pad. This is useful to simulate noise in a pad's signal or fluctuations in pedal presses
  - Press any other key to trigger a hit of the monitored pad

## FAQ
#### Windows 10 NCM device driver
- **Question:** I cannot reach the EavesDrum WebUI. Why doesn't Windows 10 detect the board as an USB network device?
- **Answer:** Windows 10 only supports legacy RNDIS USB network devices out-of-the-box. But RNDIS is not supported by macOS. That is why newer USB network devices like EavesDrum use NCM which is supported natively by all modern OS like macOS, Linux and Windows 11. Although Windows 10 comes with the drivers for NCM, they have to be installed manually. [See this issue to find instructions how to do this.](https://github.com/tobigun/EavesDrum/issues/4#issuecomment-3537404783)

#### LEDs
- **Question:** What do the LEDs on the board mean?
- **Answer:**
  - The red (LED1) is the Network LED. If it lights up, the network (either USB or WiFi) is up. It blinks when data is transferred. Maybe a bit misleading but if you see a red light that is good.
  - The LED next to it (LED2) is the hit indicator. It should blink whenever you hit a pad.
  - Finally, the green LED on the Pico indicates that Midi is working (this is only useful if you use Bluetooth Midi).

## About This Project
Originally I started EavesDrum as I wanted to improve my Guitar Hero Drum Kit and make it less noisy. So I built my own mesh drum for this kit out of tin cookie jars, some pollen screen (which is better suited than fly screen) and some piezos. Although it might not give you the feel and rebound of a real drum, it was at least very quiet ;-)

The next step was to try my DIY drums with a software drum module but I soon discovered that drum gear (especially drum modules) is just too expensive for experimentation. So I built my own trigger module. First I started with [Hello Drum](https://github.com/RyoKosaka/HelloDrum-arduino-Library) but as it did not work as expected I wrote my own firmware from scratch.

Over the course of a year, I continuously improved and redesigned the hardware and software. Whenever there was a discount I bought "real" drum pads to test it. After some time I had a full drum kit mixed with a lot of drums and cymbals (rubber and low volume) from different vendors (a Frankenstein drum kit so to speak).

In my opinion, most drum modules and kits are a bit too pricey for what they offer (as the cost of a piezo is below 1€) - especially if you just want to start drumming. So I open sourced the project to minimize the entry barrier into this nice hobby.

Note that this project is not meant to compete with drum modules or gear from drum manufacturers like Roland, EFNote or Yamaha. It is more an addition for makers who like DIY. If you want to perform live you want the safety that your gear works at all times - something that this project cannot offer. As I work in the embedded industry I know that reliability needs a lot of testing and experience - so this costs a lot of money that you pay in the end when you buy a product.

So if you have the money, give a little love to the drum vendors and buy some original equipment in addition to your DIY stuff.

## Other Related Projects
- [Hello Drum](https://github.com/RyoKosaka/HelloDrum-arduino-Library) by  Ryo Kosaka
  - A nice Open Source trigger module for ESP32 and Arduino with DIY drum pads (https://open-e-drums.com/)
  - Unfortunately the last commit is 5 years old and it did not work with my cymbals
- [Edrumulus](https://github.com/corrados/edrumulus) by Volker Fischer (corrados)
  - Another Open Source trigger module for ESP32 and Teensy with Positional sensing and Cross talk cancellation

## Libraries

The following libraries are used in this project:

- Arduino-Pico framwork by earlephilhower 
  - LGPL-2.1 license (Copyright: Earle F. Philhower, III)
- Pico-SDK
  - BSD 3-Clause license (Copyright: Raspberry Pi (Trading) Ltd)
- fortyseveneffects / MIDI Library
  - MIT license (Copyright: Francois Best)
- tobozo / YAMLDuino
  - MIT License: https://github.com/tobozo/YAMLDuino?tab=License-1-ov-file#readme
- bblanchon / ArduinoJson
  - MIT License (Copyright: Benoit BLANCHON)
- hathach / tinyusb
  - MIT License (Copyright: hathach (tinyusb.org))
- lwip-tcpip / lwip
  - BSD-3-Clause license (Copyright: Swedish Institute of Computer Science)
- littlefs-project / LittleFS
  - BSD-3-Clause license (Copyright: The littlefs authors / Arm Limited. All rights reserved)
- ESP32Async / ESPAsyncWebServer
  - LGPL-3.0 license (Copyright: ESP32Async)
- ayushsharma82 / RPAsyncTCP
  - LGPL-3.0 license (Copyright: Ayush Sharma, Khoi Hoang, Hristo Gochkov)
- sekigon-gonnoc / Pico-PIO-USB
  - MIT License (Copyright: sekigon-gonnoc)  
- rppicomidi / pico-w-ble-midi-lib
  - MIT License (Copyright: rppicomidi)  
- rppicomidi / ring_buffer_lib
  - MIT License (Copyright: rppicomidi)  
- wiimote-lib (Loc15/PicoGamepadConverter, Original: rnconrad/WiimoteEmulator)
  - GPLv3 License (Original: unknown)  
- LUFA hidparser (from abcminiuser with changes by Santroller)
  - MIT License (Copyright: Dean Camera)  
- cesanta / mongoose (PC simulation only)
  - GPLv2 License (Copyright: Sergey Lyubka / Cesanta Software Limited)    

Uses information from these projects:
- PlasticBand Instrument Peripheral Documentation by TheNathannator (Nathan), Sanjay Govind, et al.
  - Github: https://github.com/TheNathannator/PlasticBand
  - Creative Commons Attribution-ShareAlike 4.0 International License
- Rock Band MIDI-to-USB Drum Controller for Nintendo Wii from Ken Kurzweil
  - Github: https://github.com/kurzweil/MidiRock
  - MIT License (Copyright: Rock Band MIDI-to-USB Drum Controller Contributors)  

## Author
Tobias Gunkel
- GitHub: [tobigun](https://github.com/tobigun)
- Mail: [tobias@eavesdrum.io](mailto:tobias@eavesdrum.io)

## License
This project is licensed under the [GNU General Public License v3.0](LICENSE.txt).
The licenses of the used libraries can be viewed by clicking on the info-button in the top icon bar.

**Logo Fonts:**
- Audiowide
  - https://fonts.google.com/specimen/Audiowide
  - Copyright (c) 2012, Brian J. Bonislawsky DBA Astigmatic (AOETI) (astigma@astigmatic.com)
  - SIL Open Font License, Version 1.1
- Philosopher
  - https://fonts.google.com/specimen/Philosopher
  - Designed by Jovanny Lemonad
  - Copyright 2011 The Philosopher Project Authors (https://github.com/alexeiva/philosopher)
  - SIL Open Font License, Version 1.1

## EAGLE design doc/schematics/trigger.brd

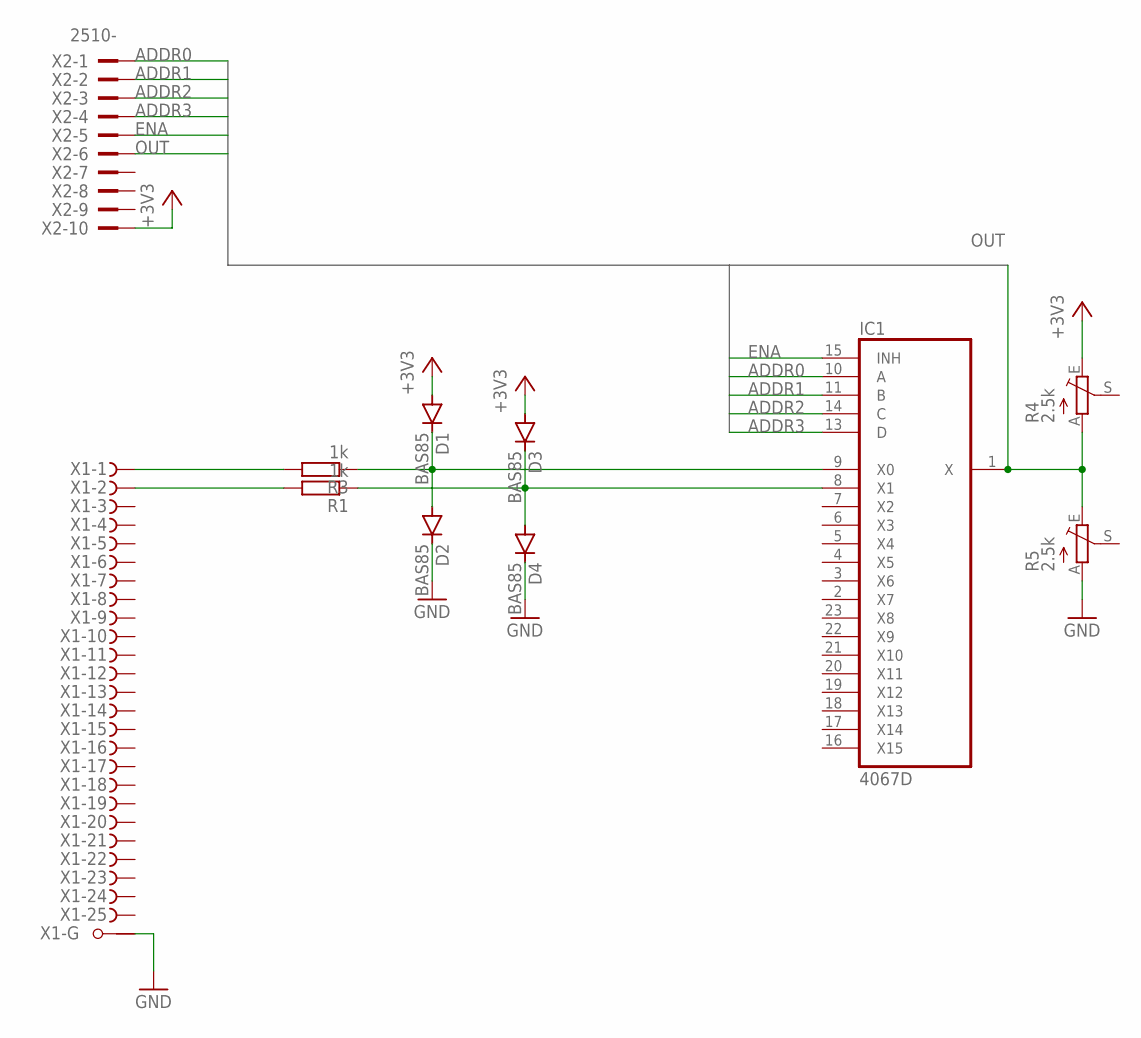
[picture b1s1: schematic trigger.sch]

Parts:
D1, D2, D3, D4: BAS85; SOD80C
IC1: 4067D; SO24W
R1, R3: 1k; 0204/7
R4, R5: 2.5k; PT-10
X1: F25HPS; F25HP
X2: 2510-; PAK100/2500-10

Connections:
+3V3: D1.A, D3.A, R4.E, X2.10
ADDR0: IC1.10 (A), X2.1
ADDR1: IC1.11 (B), X2.2
ADDR2: IC1.14 (C), X2.3
ADDR3: IC1.13 (D), X2.4
ENA: IC1.15 (INH), X2.5
GND: D2.C, D4.C, R5.A, X1.G1
unnamed: R3.2, X1.1 (F)
unnamed: D1.C, D2.A, IC1.9 (X0), R3.1
unnamed: R1.2, X1.2 (F)
unnamed: D3.C, D4.A, IC1.8 (X1), R1.1
OUT: IC1.1 (X), R4.A, R5.E, X2.6
VDD: IC1.24 (VDD)
VSS: IC1.12 (VSS)

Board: 2 copper layers, 11 parts (0 on the bottom side), 12 nets, no tracks yet.

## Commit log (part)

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2025-08-03 use absolut imports
2025-08-03 move settings to pad again
2025-08-04 update esp32
2025-08-05 adjust hihat schematic
2025-08-05 adjust module schematics
2025-08-06 fix pcba issues
2025-08-06 update esp32 sdk
2025-08-06 add schema for config
2025-08-06 move mappings
2025-08-06 add mapping for ezdrummer
2025-08-07 add mappings
2025-08-07 move presets
2025-08-30 update resistor values
2025-08-30 update pico arduino
2025-08-30 update usb descriptor
2025-08-30 reset usb on boot and perform led test
2025-09-07 uodate dependencies
2025-09-07 add undefined mapping value and move mappings out of pad
2025-09-07 remove pedal chick flag
2025-09-07 check for tinyusb
2025-09-07 disable unimplemented cross note detection in ui
2025-09-07 fix TODO
2025-09-07 check for padIndex in cross-stick
2025-09-07 show unused mappings
2025-09-07 fix dirty flag
2025-09-07 make connector selectable via ui
2025-09-07 handle invalid roles
2025-09-08 make roles and names editable
2025-09-08 add pad type selector to mappings
2025-09-08 reformat role
2025-09-08 improve representation of roles
2025-09-09 cleanup ediztable header
2025-09-10 make role names configurable
2025-09-11 reset mappings if mappings file is uploaded
2025-09-12 configs can be replaced via ui now
2025-09-17 fix ambiguous initialization
2025-09-17 update vite
2025-09-22 add cymbal 3+4 and tom 4+5
2025-09-23 fix pedal by inversion
2025-09-23 fine-tune config
2025-09-23 add more debug output
2025-09-24 reformat config to match UI format
2025-09-24 handle config download in ui
2025-09-24 validate uploads
2025-09-24 flush muxers on demand
2025-09-26 add missing license
2025-09-26 update spice model
2025-09-26 do not flush mux if simulated
2025-09-26 add missing restriction for choke type
2025-09-27 update documentation
2025-09-27 Update README.md
    fix important section
2025-09-27 add more results
2025-09-27 more readme
2025-09-27 fix spelling
2025-09-27 fix grammar
2025-09-27 fix style
2025-09-27 update presets
2025-09-27 update docu
2025-09-27 change figure labels
2025-09-28 replace schema url
2025-09-28 fix images
2025-09-28 More fixes
2025-09-28 try to fix indentation
2025-09-28 embed font into logo
2025-09-28 replace favicon
2025-09-28 show error message if resource is not found
2025-09-28 abort on error
2025-09-28 fix build pipeline
2025-09-29 replace erlang uf2tool with python script
2025-09-29 update pio pico
2025-09-29 switch order of fs and fw in uf2 file to fix pico1 issues with missing ui
2025-09-29 finalize build
2025-09-29 set version to 1.0.0
2025-09-29 add hihat instructions
2025-09-30 add github pages config
2025-09-30 update pages
2025-09-30 add plugins
2025-09-30 readd includes dir
2025-09-30 update github pages
2025-09-30 update github
2025-09-30 fiw md links
2025-10-02 change unsupported info to note
2025-10-09 add info about me
2025-10-12 add more latency results
2025-10-19 update to newest pico framework
2025-10-19 keep config after flashing new fw
2025-11-12 Add YouTube trailer link to README
    Added a YouTube trailer link to the README.
2025-11-16 module schematic v1.1.1: use header instead of pico
2025-11-16 add efnote pinout
2025-11-16 rename module schematics
2025-11-17 fix link to schematics
2025-11-17 fix anchor
2026-02-01 Update issue templates
2026-03-06 update libraries
2026-03-06 add bt midi lib
2026-03-09 add debug macro to ble_midi
2026-03-09 disable usage cyw43 led
2026-03-10 update ui deps
2026-03-15 add support for midi output modes
2026-03-16 add support for ble server
2026-03-17 centralize access to serial port
2026-03-17 fix wireless model detection
2026-03-20 bugfixes
2026-03-20 support for 5-pin din Midi and Guitar Hero Drums
2026-03-20 improve text for section for "Pads with undefined Roles"
2026-03-21 move ble client update method to ble midi transport update
2026-03-21 add support for wifi network
2026-03-21 use Ble LED for Midi connection in general
2026-03-21 replace watchdog LED with watchdog timer
2026-03-21 rename usb to usb client
2026-03-22 poll usb device task manually
2026-03-22 ckeanup io
2026-03-22 add USB-Host Midi
2026-03-22 cleanup
2026-03-22 cleanup esp32
2026-03-22 correct LED polarity
2026-03-22 fix endless loop in midi transport
2026-03-22 map din serial to expansion slot
2026-03-22 fix USB host crashes
2026-03-22 try to fix USB Host freezes
2026-03-22 fix unit tests
2026-03-22 update github flow actions
2026-03-22 add pico2w
2026-03-23 remove picow: does not have enough RAM for parsing yaml
2026-03-23 disable picow
2026-03-23 implement panic in AsyncTCP
2026-03-23 Bugfix #5: fix config upload discarded if config is sent in multiple chunks
2026-03-23 add PICO-PIO to licenses
2026-03-23 stabilize usb network connection
2026-03-23 reduce warnings during test
2026-03-23 fix native build and cleanup WS handling
2026-03-23 cache esp32 build
2026-03-23 github actions: require cache name
2026-03-23 use stock lwip
2026-03-23 update ArduinoJson
2026-03-23 update yamlduino
2026-03-23 update platform pico
2026-03-23 move networking to lib folder
2026-03-25 rename base circuit schematics
2026-03-25 add connector schematics
2026-03-25 schematics for module 1.2
2026-03-26 update schematics
2026-03-26 move schematics
2026-03-26 add note for revision 1.2
2026-03-27 minor schematic change
2026-03-27 update gitignore
2026-03-28 make sure a even single points (in between gaps) in the graph are visible
2026-03-28 move touch code
2026-03-30 add touch support
2026-03-30 tinyusb networking is used as a lib now
2026-03-30 embed jsonc as resource
2026-03-30 improve documentation
2026-03-30 fix esp32 and native build
2026-03-31 update touch
2026-04-01 add banner for Europe Drum Show
2026-04-02 add efnote conenctor pinout
2026-04-03 add more statistics
2026-04-03 fix build
2026-04-03 move general config to own file
2026-04-03 add board version
2026-04-03 copy SerialUART for TX only Serial
2026-04-03 rename
2026-04-03 Do not use RX pin for MIDI Serial
2026-04-03 select MIDI TX pin depending on board version
2026-04-03 fix readme
2026-04-03 fix board version loading
2026-04-04 add shirt svg
2026-04-04 fix json schema
2026-04-04 fix statistics texts
2026-04-05 try to fix banner
2026-04-05 fix banner
2026-04-05 tested with iOS
2026-04-05 change choke types according to pad type
2026-04-05 update schema version
2026-04-05 avoid intepretation of board version as number
2026-04-06 move board specific files
2026-04-06 change readme for board 1.2
2026-04-06 use board 1.1 as default
2026-04-06 fix watchdog due to non-stopping BLE server
2026-04-06 add support for touch choke for piezo cymbals
2026-04-07 add latency measurements for focusrite scarlett
2026-04-07 prepare for decay time support
2026-04-08 add mapping for superior drummer
2026-04-10 remove unneccessary holes for jack connector
2026-04-14 remove link to drum show
2026-04-17 cleanup for board v1.2
2026-04-18 add info about connector PCB
2026-04-18 link connector schematics
2026-04-18 default config to hardware v1.2
2026-04-26 set version to 1.1.0
2026-04-26 Fix naming of "USB Device" in UI
2026-05-17 Refine Bluetooth LE Server section in README
    Removed redundant text and clarified BLE Server mode usage for Windows.
2026-05-26 wiimote-lib: add support for guitar hero drums
2026-05-26 pico: support more buttons
2026-05-26 increase flush time as bt classic takes quite long to send interrupts
2026-05-26 add wiimote-lib from Loc15/PicoGamepadConverter
2026-05-26 add raw log level (for logging in external libs to DebugSerial)
2026-05-26 fix wrong log levels in ui
2026-05-26 remove ble_midi_server.h from header to avoid conflicting hid definitions (ble vs usb)
2026-05-26 rename midi transport gh to gh spi
2026-05-26 add used libraries section to readme
2026-05-26 add support for wii guitar hero drum
2026-05-26 fix and stabilize wiimote-lib
2026-05-26 use ATTR_PACKED macro
2026-05-26 move usb host code to own file
2026-05-26 remove redundant noInterrupts call from config mapper
    This is already called by the flash library
2026-05-26 add support for USB Host HID gamepads
2026-05-27 support for wii rockband drums
2026-05-28 unify device name handling for HID and MIDI USB Host mode
2026-05-30 try to fix jekyll build
2026-06-02 share mapping between all GH/RB variants
2026-06-03 add generic gamepad mode
2026-06-07 fix: send monitor data of previous hit if new hit detected
2026-06-07 ui: make year a pattern in copyright notice
2026-06-07 Add decay phase
2026-06-07 use max value during scan time in decay curve instead of hit value
2026-06-17 fix closed notes
2026-06-17 add decayTimeMs/decayType to jsonc
2026-06-17 add FAQ

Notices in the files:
README.md:
This project is licensed under the [GNU General Public License v3.0](LICENSE.txt).
The licenses of the used libraries can be viewed by clicking on the info-button in the top icon bar.
Logo Fonts:
- Audiowide
- https://fonts.google.com/specimen/Audiowide
- Copyright (c) 2012, Brian J. Bonislawsky DBA Astigmatic (AOETI) (astigma@astigmatic.com)
- SIL Open Font License, Version 1.1
- Philosopher
- https://fonts.google.com/specimen/Philosopher
- Designed by Jovanny Lemonad
- Copyright 2011 The Philosopher Project Authors (https://github.com/alexeiva/philosopher)
- SIL Open Font
